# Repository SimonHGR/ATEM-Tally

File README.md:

# ATEM Tally

Remote control / live channel monitor for Blackmagic ATEM devices

Uses ESP 8266 to select one of four inputs on the ATEM switcher, 
and light a "tally" lamp to indicate which channel is selected. 

Operates using the Blackmagic Router Control Protocol described
in [this video](https://www.youtube.com/watch?v=K3Jx0jbtick&t=131s)

Circuit & PCB layout created in KiCad 5.1.7

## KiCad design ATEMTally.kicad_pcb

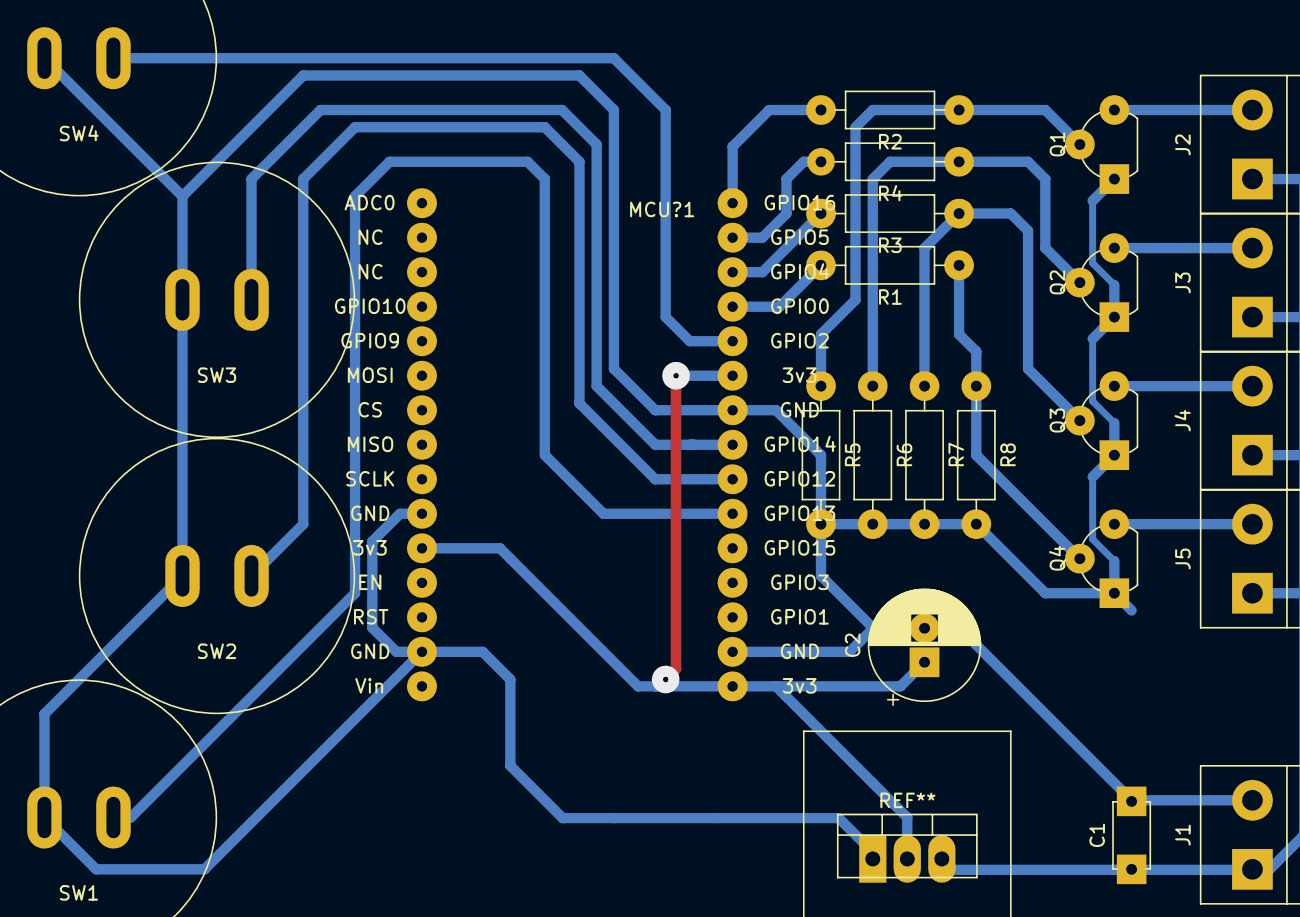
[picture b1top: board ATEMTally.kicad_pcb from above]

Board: 2 copper layers, 25 parts (0 on the bottom side), 19 nets.

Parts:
C1: 100nF; C_Disc_D4.7mm_W2.5mm_P5.00mm
C2: 10uF; CP_Radial_D8.0mm_P2.50mm
J1: 12 V Power; TerminalBlock_bornier-2_P5.08mm
J2, J3, J4, J5: ToLED; TerminalBlock_bornier-2_P5.08mm
MCU?1: NodeMCU
Q1, Q2, Q3, Q4: 2N7000; TO-92L_Wide
R1, R2, R3, R4: 1k; R_Axial_DIN0207_L6.3mm_D2.5mm_P10.16mm_Horizontal
R5, R6, R7, R8: 100K; R_Axial_DIN0207_L6.3mm_D2.5mm_P10.16mm_Horizontal
SW1, SW2, SW3, SW4: SW_Push; PushButton
U1: LD1117S33TR_SOT223; TO-220-3-Heatsink

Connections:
+3V3: C2.1, MCU?1.11, MCU?1.16, MCU?1.25, U1.2
+12V: C1.1, J1.1, J2.1, J3.1, J4.1, J5.1, U1.3
GND: C1.2, C2.2, J1.2, MCU?1.10, MCU?1.14, MCU?1.17, MCU?1.24, Q1.1, Q2.1, Q3.1, Q4.1, R5.2, R6.2, R7.2, R8.2, SW1.2, SW2.2, SW3.2, SW4.2, U1.1
unnamed: J2.2, Q1.3
unnamed: J3.2, Q2.3
unnamed: J4.2, Q3.3
unnamed: J5.2, Q4.3
unnamed: MCU?1.21, SW1.1
unnamed: MCU?1.22, SW2.1
unnamed: MCU?1.23, SW3.1
unnamed: MCU?1.26, SW4.1
unnamed: MCU?1.27, R1.2
unnamed: MCU?1.28, R3.2
unnamed: MCU?1.29, R4.2
unnamed: MCU?1.30, R2.2
unnamed: Q1.2, R2.1, R5.1
unnamed: Q2.2, R4.1, R6.1
unnamed: Q3.2, R3.1, R7.1
unnamed: Q4.2, R1.1, R8.1

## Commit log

2020-11-25 Initial
2020-11-25 Initital README
2020-11-25 Cleanup/Comments
2020-11-30 Modified input triggers to match PCB, corrected sense of signal output
2020-11-30 Added circuit schematic and PCB layout
2020-12-03 Added blink on inactive channels to get attention
